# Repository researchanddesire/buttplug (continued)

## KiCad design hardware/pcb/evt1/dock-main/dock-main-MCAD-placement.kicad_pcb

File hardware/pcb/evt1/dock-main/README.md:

# Shared dock main PCB candidate

`dock-main.kicad_pcb` combines the 48 source-power, 44 controller and 58 safety electrical references on one four-layer, 1.00 mm board, with six mechanical holes. The original leaf circuits remain the schematic authority. The frozen routed board passes full native KiCad10.0.8 DRC with zero violations and zero unconnected items. Final source-bound checks and the saved-copper resistance report establish the digital candidate; this folder is not a fabrication release.

The fabrication quote candidate requests finished outer copper ≥35 µm, inner copper ≥30 µm, finished via bore ≥0.15 mm and via-wall plating ≥25 µm. Nominal “1 oz” labels do not establish these minima; supplier acceptance remains false. In1 is reserved for continuous ground; In2 contains separated power distribution and low-speed routes. F.Cu/B.Cu carry the remaining signals. Ordinary trace/clearance minima are 0.15/0.15 mm, with 0.50/0.20 mm through vias. The global hole clearance is 0.20 mm. `dock-main.kicad_dru` permits 0.15 mm only between J101-owned features to preserve the USB4105 manufacturer pattern, whose actual spacing is about 0.1751 mm; fabricator acceptance remains required.

The [bench quote packages](assembly-quote/README.md) bind the routed Main
to the matching 3.65 Ω UV boards and include bare-board and assembly options.

The source block's 192 copper objects are retained, along with all 207 main critical objects. Of 59 subsequently authored fanout objects, one graph-redundant one-layer via was retired; the remaining 58 retain their exact geometry and identities. `critical-routing.json` records the authored clock, local bypass, ADC and cut-switch power connections. The approved U615/H706 adjustment is bounded by `routing/u615-bounded-exception.json`. Short residual pad escapes and three ground stitches are recorded separately. `check_main.py` checks the saved native pad/net map, protected copper, screw-head clearances and complete native DRC without ignored checks or exclusions. It can explicitly refresh a regenerated schematic XML binding only after matching all 150 native references and every physical electrical pad.

The frozen `dock-main-MCAD-placement.kicad_pcb` is the StepUp input for parallel mechanical integration. It is a placement/model snapshot, not the final routed fabrication board. `mcad-placement-handoff.json`, `mcad-model-coverage.json` and `mcad-model-checks.json` bind its 138 physical package models and 12 copper-only positions. `check_mcad_geometry.py` compares the working board's outline, holes, component poses, pads, model transforms and actual model-file hashes against that snapshot.

The frame is `dockX = pcbX - 100`, `dockY = 200 - pcbY`, F.Cu toward dock +Z. Board bottom/top are Z5.4/6.4 mm. Bounds are X−48…48, Y−4…68 mm; the native bounding-box centre (100,168) maps to dock (0,32). The four original Ø2.3 mm holes remain at (−8,5.5), (8,5.5), (−8,23.5), (8,23.5); rear holes are (−44,64) and (44,55.7). Each retains an R3 surface copper/via hardware clearance. U615 is at (42,49.5); both selected horizontal GH header positions remain unchanged.

All package STEP files are local under `DockMain.3dshapes/`. They are attributed KiCad package-family models, four primary-dimensional TI package reconstructions and a selected USB4105 1.20 mm stake derivative. The custom parts have editable FreeCAD multi-body sources. They are not exact OEM CAD or received-part qualification. Sources, dimensions, omissions and licenses are recorded in `model-plan.json` and the model provenance files. The USB face remains at X0/Y−5 with its seating plane at Z6.4. Selected nominal stakes reach Z5.2; the manufacturer's ±0.15 mm stake tolerance still needs physical clearance qualification. The old Z5.1 datum is the enclosure window bottom.

The adopted power candidate uses a 4.10 V minimum driver input and a 50 mΩ hot/aged common PCB supply-plus-return allowance. `power-study/` contains native filled-copper masks, actual neck/via calculations and the independent DC tradeoff. `MFG-SPEC.md` and `build-constraints.json` state the requested finished minima and explicit supplier review of the native 0.10 mm J101 annular feature / bounded 0.15 mm hole-clearance pattern. The fabricator must confirm the dielectric build and process limits. The inner layers must not silently use 0.5 oz copper. Shared copper is charged at full source current, including device/UI/contact loops. The 70% efficiency assumption, current limits, startup/inrush, USB suspend/source changes and all hot/aged path limits require hardware measurements. Optical leakage, temperature, material aging and cleaning efficacy remain separate validation gates; no sterilization or powered result is claimed.

`build_main.py` is a guarded placement builder and refuses to overwrite routed work. Do not restart placement to refresh a report. `route_main.py` exchanges only supported wire/via records; its residual mode retains all completed native nets and every protected item. `fill_main.py` clears stale fill caches before rebuilding connectivity and asserts that refill preserves every authored copper net. The generic automatic stub-cleanup loop was stopped by approval review. The final single-segment removal used independent owner/root/peer terminal-path evidence, a fixed input SHA/UUID, and assertions that every other copper signature and zone identity remained intact. Future stub mutations require exact reviewed UUIDs and input SHA. Historical router checkpoints and preflight reports are development evidence, not acceptance reports. Only a current, source-bound final `native-checks.json` can establish complete digital routing checks.

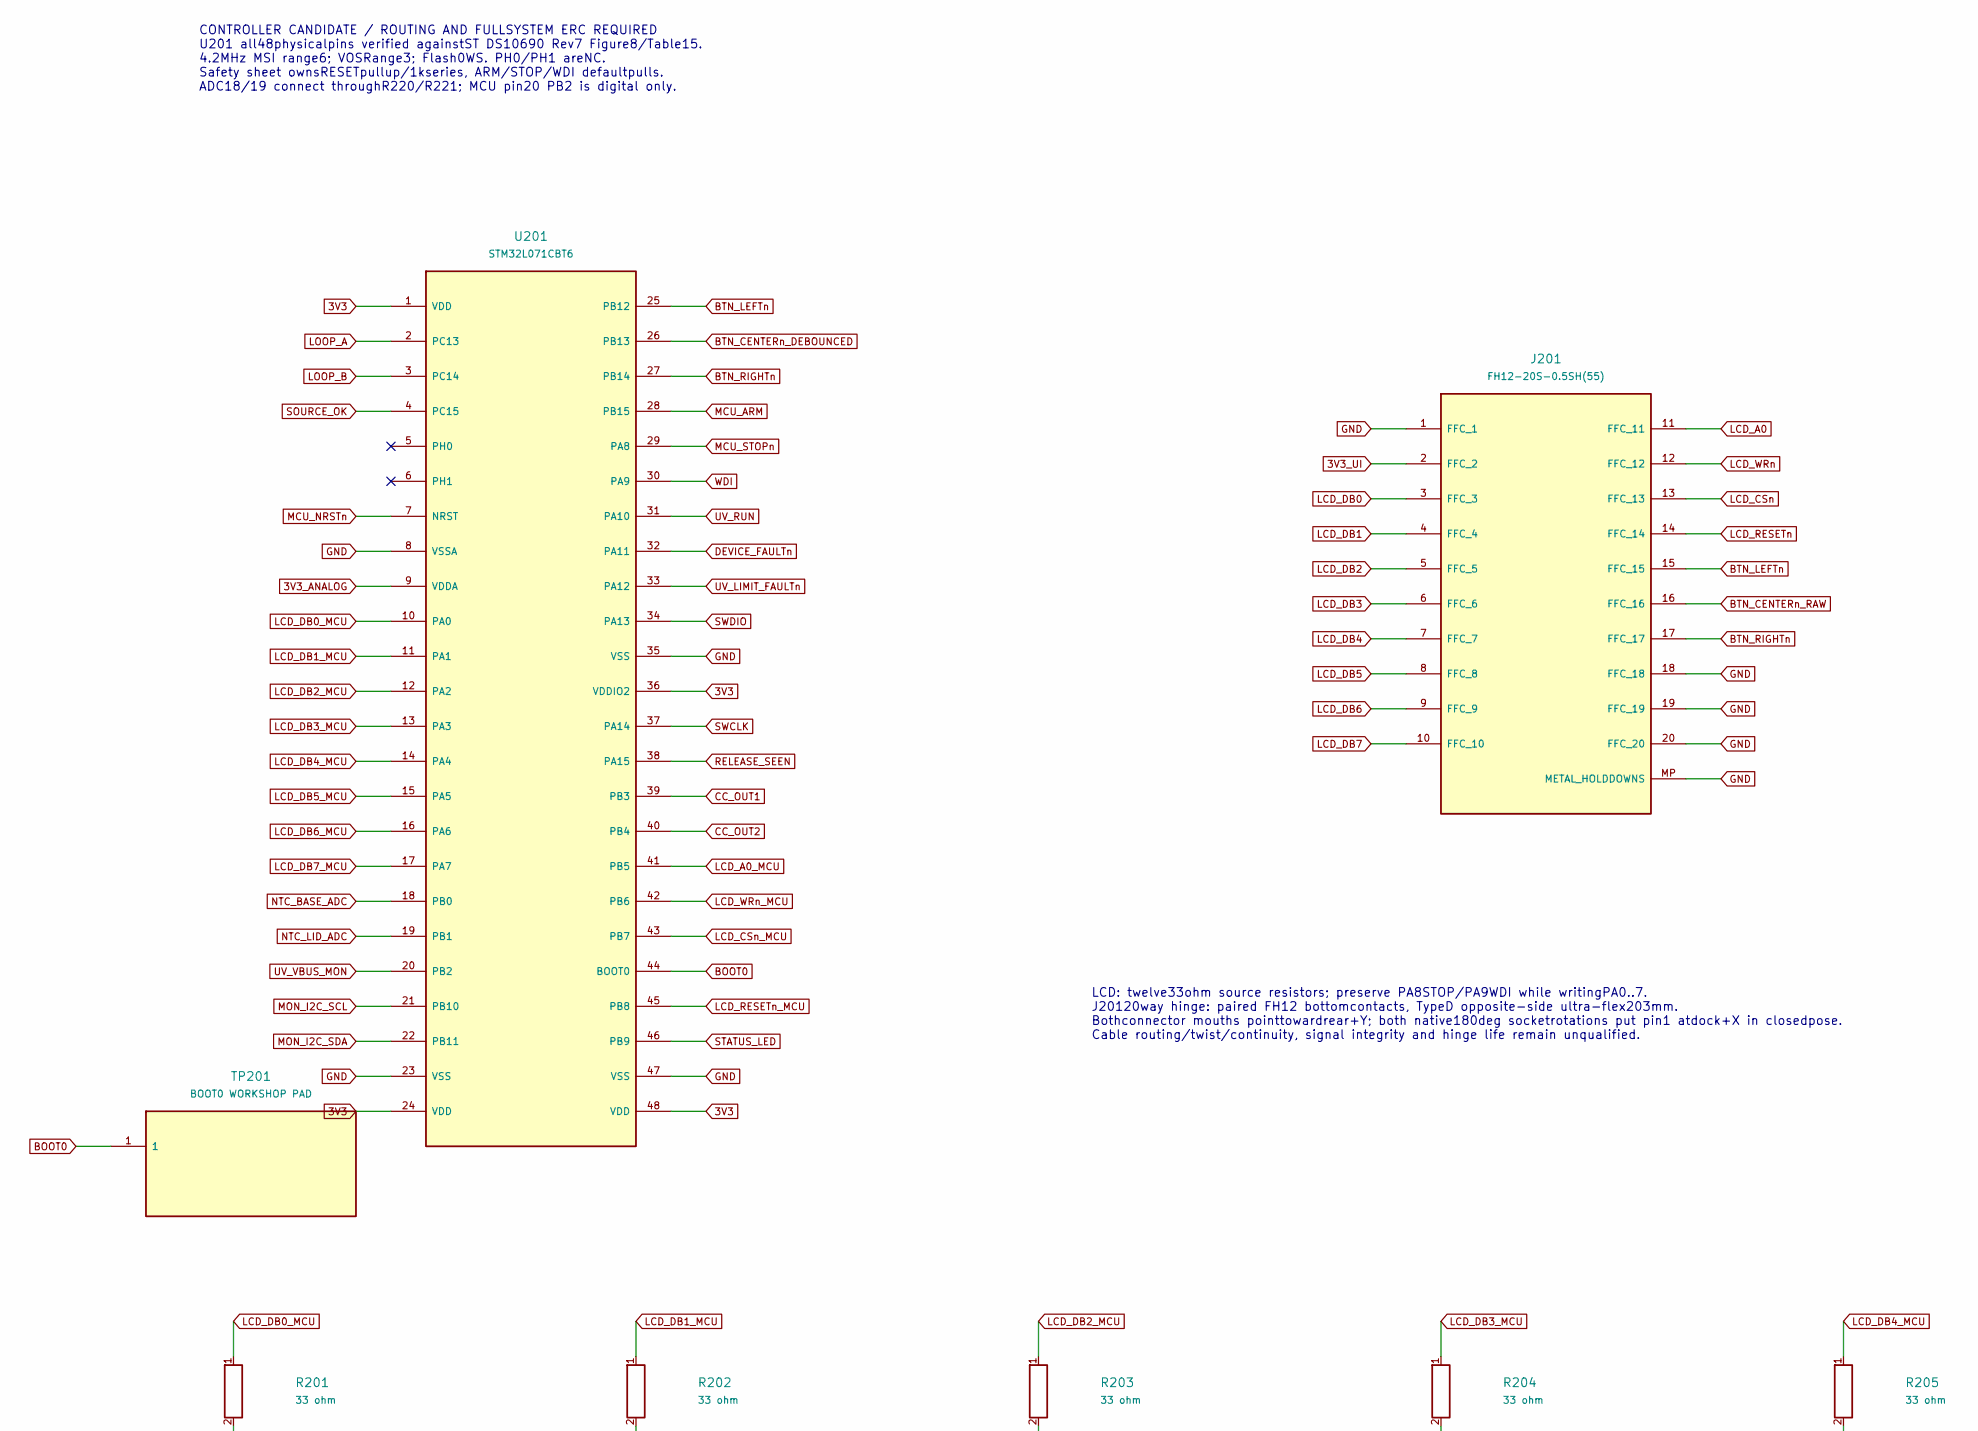
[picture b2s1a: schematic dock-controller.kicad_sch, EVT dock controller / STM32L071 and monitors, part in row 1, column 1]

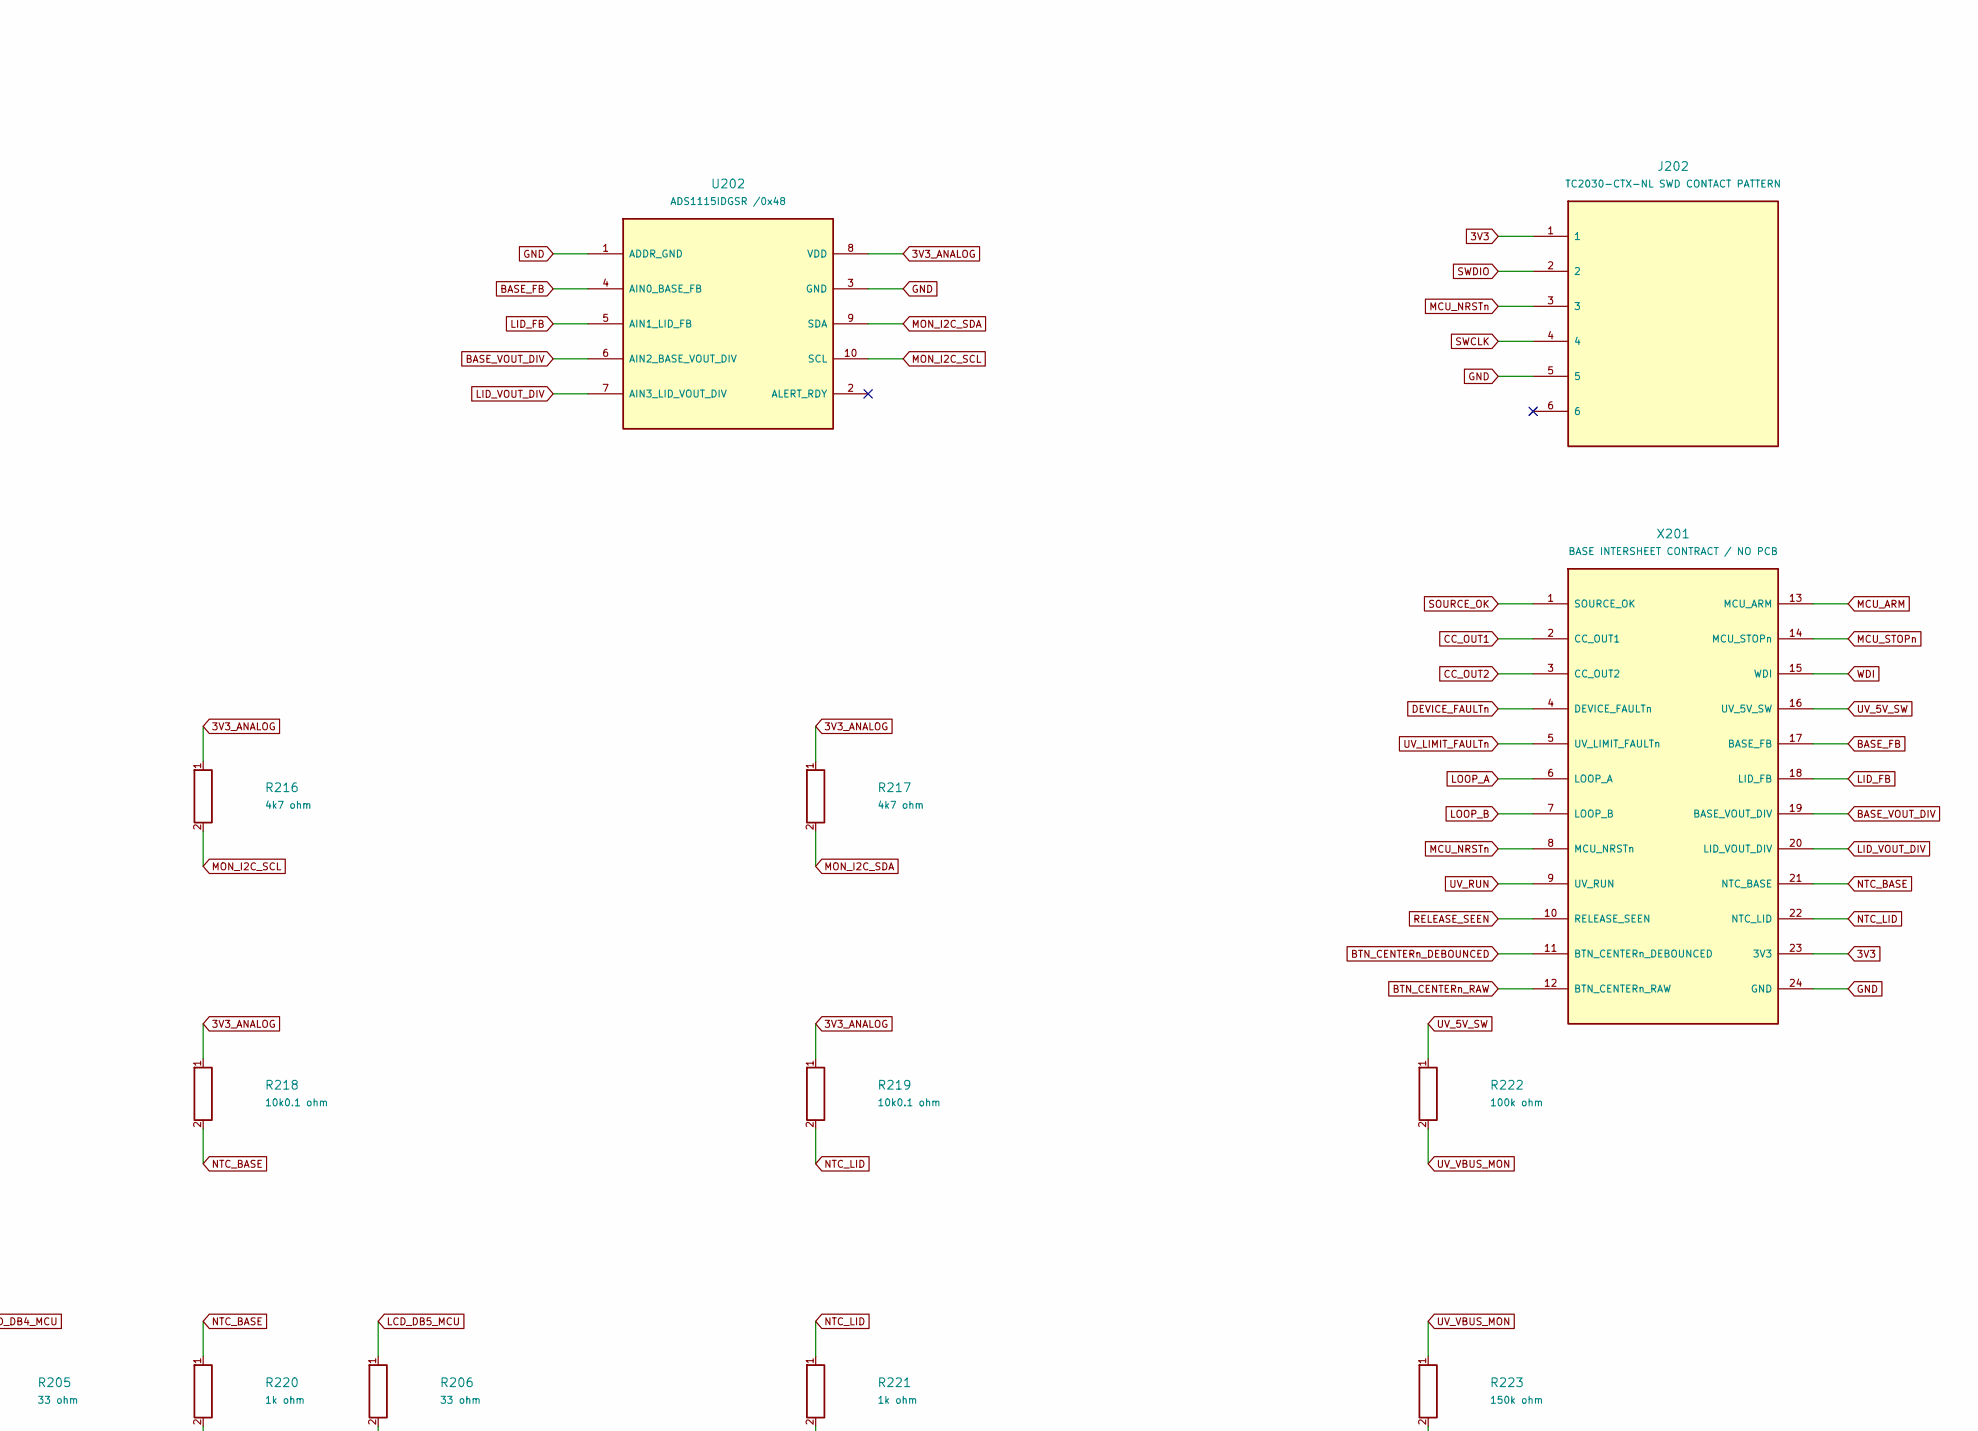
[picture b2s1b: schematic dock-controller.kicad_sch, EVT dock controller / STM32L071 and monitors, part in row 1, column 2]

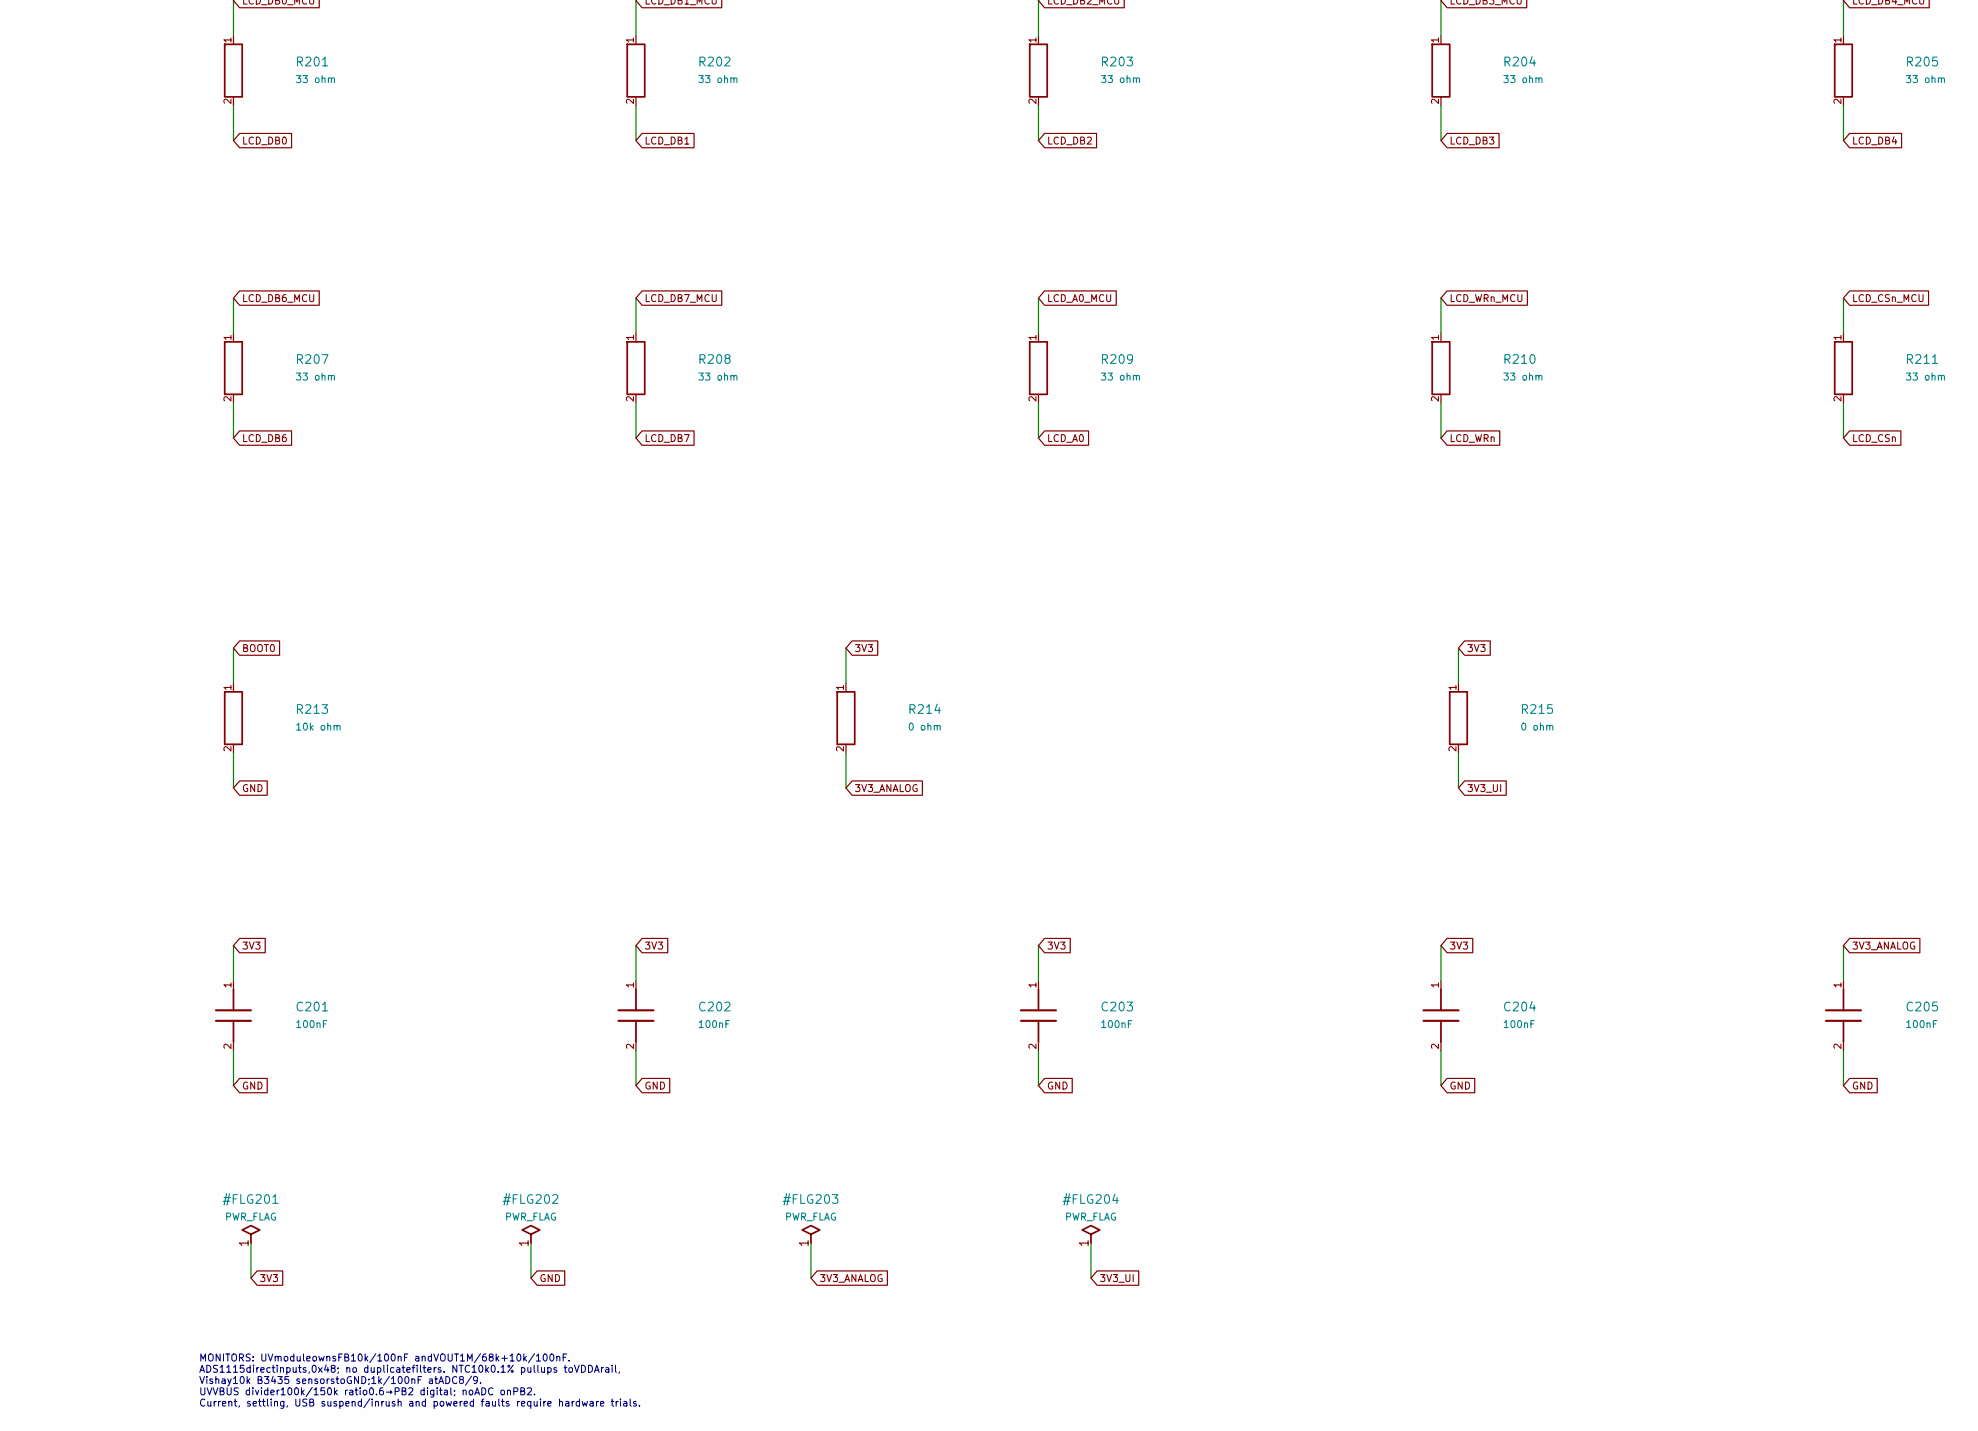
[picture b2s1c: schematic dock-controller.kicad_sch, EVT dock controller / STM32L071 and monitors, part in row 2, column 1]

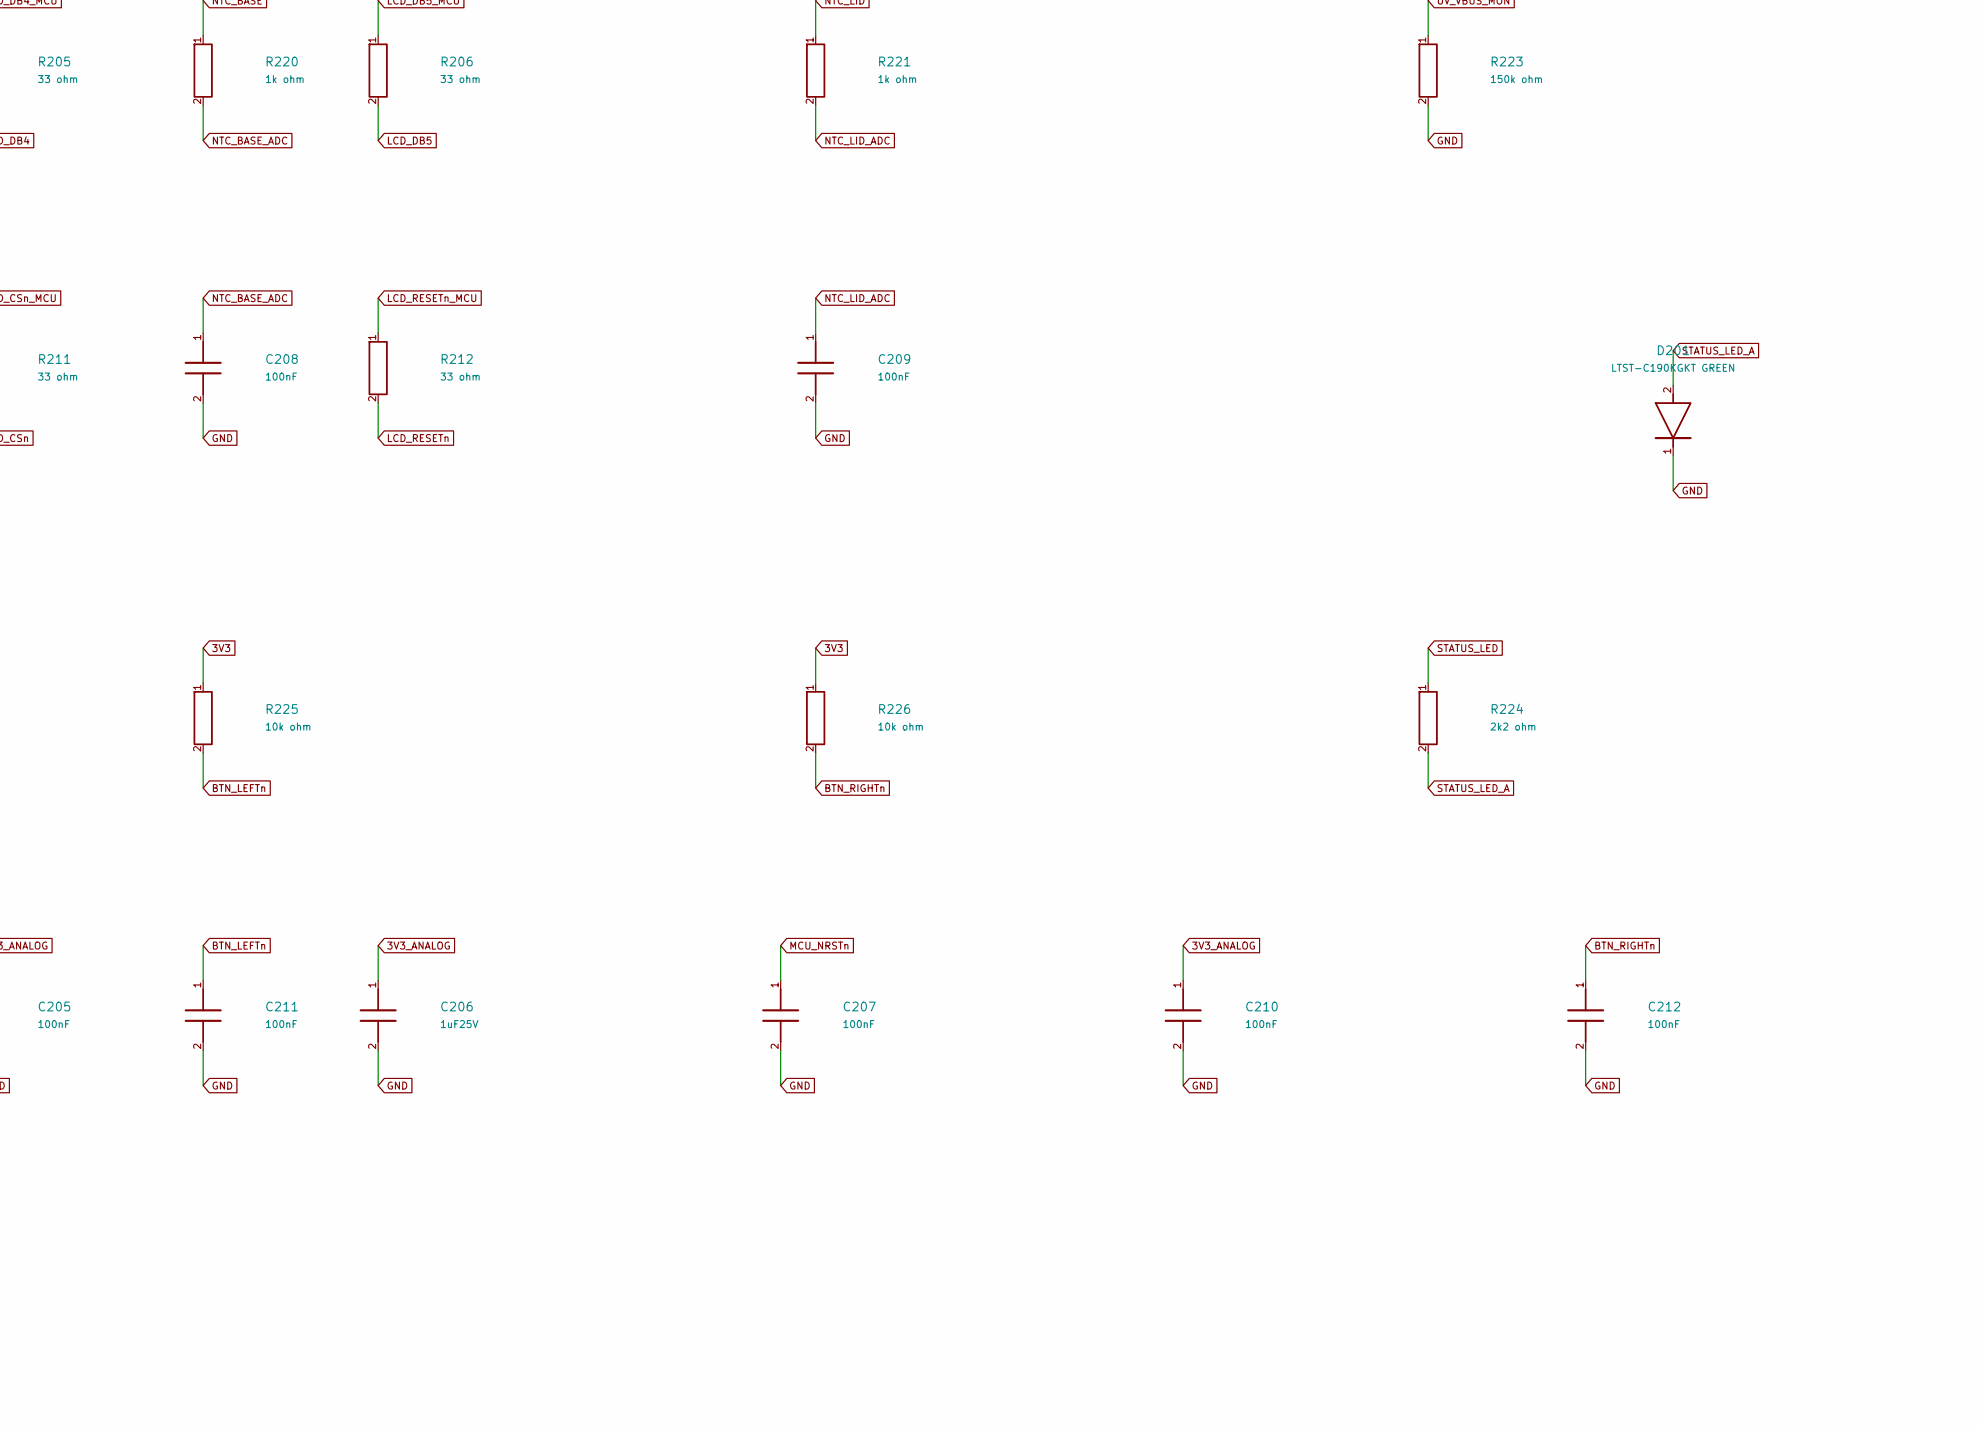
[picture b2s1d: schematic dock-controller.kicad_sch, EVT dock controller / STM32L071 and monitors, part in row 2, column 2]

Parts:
C201, C202, C203, C204, C205, C207, C208, C209, C210, C211, C212: 100nF; C_0402_1005Metric; MPN GRM155R71C104KA88D
C206: 1uF25V; C_0603_1608Metric; MPN C1608X7R1E105K080AB
D201: LTST-C190KGKT GREEN; LED_0603_1608Metric; MPN LTST-C190KGKT
J201: FH12-20S-0.5SH(55); Hirose_FH12-20S-0.5SH_1x20-1MP_P0.50mm_Horizontal; MPN FH12-20S-0.5SH(55)
J202: TC2030-CTX-NL SWD CONTACT PATTERN; Tag-Connect_TC2030-IDC-NL_2x03_P1.27mm_Vertical; MPN –
R201, R202, R203, R204, R205, R206, R207, R208, R209, R210, R211, R212: 33 ohm; R_0603_1608Metric; MPN RC0603FR-0733RL
R213, R225, R226: 10k ohm; R_0603_1608Metric; MPN RC0603FR-0710KL
R214, R215: 0 ohm; R_0603_1608Metric; MPN RC0603JR-070RL
R216, R217: 4k7 ohm; R_0603_1608Metric; MPN RC0603FR-074K7L
R218, R219: 10k0.1 ohm; R_0603_1608Metric; MPN RT0603BRD0710KL
R220, R221: 1k ohm; R_0603_1608Metric; MPN RC0603FR-071KL
R222: 100k ohm; R_0603_1608Metric; MPN RC0603FR-07100KL
R223: 150k ohm; R_0603_1608Metric; MPN RC0603FR-07150KL
R224: 2k2 ohm; R_0603_1608Metric; MPN RC0603FR-072K2L
TP201: BOOT0 WORKSHOP PAD; TestPoint_Pad_D1.0mm; MPN –
U201: STM32L071CBT6; LQFP-48_7x7mm_P0.5mm; MPN STM32L071CBT6
U202: ADS1115IDGSR /0x48; VSSOP-10_3x3mm_P0.5mm; MPN ADS1115IDGSR
X201: BASE INTERSHEET CONTRACT / NO PCB; MPN –

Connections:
3V3: C201.1, C202.1, C203.1, C204.1, J202.1, R214.1, R215.1, R225.1, R226.1, U201.1 (VDD), U201.24 (VDD), U201.36 (VDDIO2), U201.48 (VDD), X201.23 (3V3); also elsewhere on the board
3V3_ANALOG: C205.1, C206.1, C210.1, R214.2, R216.1, R217.1, R218.1, R219.1, U201.9 (VDDA), U202.8 (VDD)
3V3_UI: J201.2 (FFC_2), R215.2
BASE_FB: U202.4 (AIN0_BASE_FB), X201.17 (BASE_FB); also elsewhere on the board
BASE_VOUT_DIV: U202.6 (AIN2_BASE_VOUT_DIV), X201.19 (BASE_VOUT_DIV); also elsewhere on the board
BOOT0: R213.1, TP201.1, U201.44 (BOOT0)
BTN_CENTERn_DEBOUNCED: U201.26 (PB13), X201.11 (BTN_CENTERn_DEBOUNCED); also elsewhere on the board
BTN_CENTERn_RAW: J201.16 (FFC_16), X201.12 (BTN_CENTERn_RAW); also elsewhere on the board
BTN_LEFTn: C211.1, J201.15 (FFC_15), R225.2, U201.25 (PB12)
BTN_RIGHTn: C212.1, J201.17 (FFC_17), R226.2, U201.27 (PB14)
CC_OUT1: U201.39 (PB3), X201.2 (CC_OUT1); also elsewhere on the board
CC_OUT2: U201.40 (PB4), X201.3 (CC_OUT2); also elsewhere on the board
DEVICE_FAULTn: U201.32 (PA11), X201.4 (DEVICE_FAULTn); also elsewhere on the board
GND: C201.2, C202.2, C203.2, C204.2, C205.2, C206.2, C207.2, C208.2, C209.2, C210.2, C211.2, C212.2, D201.1 (2), J201.1 (FFC_1), J201.18 (FFC_18), J201.19 (FFC_19), J201.20 (FFC_20), J201.MP (METAL_HOLDDOWNS), J202.5, R213.2, R223.2, U201.8 (VSSA), U201.23 (VSS), U201.35 (VSS), U201.47 (VSS), U202.1 (ADDR_GND), U202.3 (GND), X201.24 (GND); also elsewhere on the board
LCD_A0: J201.11 (FFC_11), R209.2
LCD_A0_MCU: R209.1, U201.41 (PB5)
LCD_CSn: J201.13 (FFC_13), R211.2
LCD_CSn_MCU: R211.1, U201.43 (PB7)
LCD_DB0: J201.3 (FFC_3), R201.2
LCD_DB0_MCU: R201.1, U201.10 (PA0)
LCD_DB1: J201.4 (FFC_4), R202.2
LCD_DB1_MCU: R202.1, U201.11 (PA1)
LCD_DB2: J201.5 (FFC_5), R203.2
LCD_DB2_MCU: R203.1, U201.12 (PA2)
LCD_DB3: J201.6 (FFC_6), R204.2
LCD_DB3_MCU: R204.1, U201.13 (PA3)
LCD_DB4: J201.7 (FFC_7), R205.2
LCD_DB4_MCU: R205.1, U201.14 (PA4)
LCD_DB5: J201.8 (FFC_8), R206.2
LCD_DB5_MCU: R206.1, U201.15 (PA5)
LCD_DB6: J201.9 (FFC_9), R207.2
LCD_DB6_MCU: R207.1, U201.16 (PA6)
LCD_DB7: J201.10 (FFC_10), R208.2
LCD_DB7_MCU: R208.1, U201.17 (PA7)
LCD_RESETn: J201.14 (FFC_14), R212.2
LCD_RESETn_MCU: R212.1, U201.45 (PB8)
LCD_WRn: J201.12 (FFC_12), R210.2
LCD_WRn_MCU: R210.1, U201.42 (PB6)
LID_FB: U202.5 (AIN1_LID_FB), X201.18 (LID_FB); also elsewhere on the board
LID_VOUT_DIV: U202.7 (AIN3_LID_VOUT_DIV), X201.20 (LID_VOUT_DIV); also elsewhere on the board
LOOP_A: U201.2 (PC13), X201.6 (LOOP_A); also elsewhere on the board
LOOP_B: U201.3 (PC14), X201.7 (LOOP_B); also elsewhere on the board
MCU_ARM: U201.28 (PB15), X201.13 (MCU_ARM); also elsewhere on the board
MCU_NRSTn: C207.1, J202.3, U201.7 (NRST), X201.8 (MCU_NRSTn); also elsewhere on the board
MCU_STOPn: U201.29 (PA8), X201.14 (MCU_STOPn); also elsewhere on the board
MON_I2C_SCL: R216.2, U201.21 (PB10), U202.10 (SCL)
MON_I2C_SDA: R217.2, U201.22 (PB11), U202.9 (SDA)
NTC_BASE: R218.2, R220.1, X201.21 (NTC_BASE); also elsewhere on the board
NTC_BASE_ADC: C208.1, R220.2, U201.18 (PB0)
NTC_LID: R219.2, R221.1, X201.22 (NTC_LID); also elsewhere on the board
NTC_LID_ADC: C209.1, R221.2, U201.19 (PB1)
RELEASE_SEEN: U201.38 (PA15), X201.10 (RELEASE_SEEN); also elsewhere on the board
SOURCE_OK: U201.4 (PC15), X201.1 (SOURCE_OK); also elsewhere on the board
STATUS_LED: R224.1, U201.46 (PB9)
STATUS_LED_A: D201.2 (1), R224.2
SWCLK: J202.4, U201.37 (PA14)
SWDIO: J202.2, U201.34 (PA13)
UV_5V_SW: R222.1, X201.16 (UV_5V_SW); also elsewhere on the board
UV_LIMIT_FAULTn: U201.33 (PA12), X201.5 (UV_LIMIT_FAULTn); also elsewhere on the board
UV_RUN: U201.31 (PA10), X201.9 (UV_RUN); also elsewhere on the board
UV_VBUS_MON: R222.2, R223.1, U201.20 (PB2)
WDI: U201.30 (PA9), X201.15 (WDI); also elsewhere on the board

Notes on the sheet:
CONTROLLER CANDIDATE / ROUTING AND FULLSYSTEM ERC REQUIRED U201 all48physicalpins verified againstST DS10690 Rev7 Figure8/Table15. 4.2MHz MSI range6; VOSRange3; Flash0WS. PH0/PH1 areNC. Safety sheet ownsRESETpullup/1kseries, ARM/STOP/WDI defaultpulls. ADC18/19 connect throughR220/R221; MCU pin20 PB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
LCD: twelve33ohm source resistors; preserve PA8STOP/PA9WDI while writingPA0..7. J20120way hinge: paired FH12 bottomcontacts, TypeD opposite-side ultra-flex203mm. Bothconnector mouths pointtowardrear+Y; both native180deg socketrotations put pin1 atdock+X in closedpose. Cable routing/twist/continuity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
MONITORS: UVmoduleownsFB10k/100nF andVOUT1M/68k+10k/100nF. ADS1115directinputs,0x48; no duplicatefilters. NTC10k0.1% pullups toVDDArail, Vishay10k B3435 sensorstoGND;1k/100nF atADC8/9. UVVBUS divider100k/150k ratio0.6→PB2 digital; noADC onPB2. Current, settling, USB suspend/inrush and powered fault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

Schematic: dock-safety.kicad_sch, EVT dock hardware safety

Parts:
C602, C606, C607, C608, C609, C610, C611, C612, C613, C614, C615, C616: 100nF16V; C_0402_1005Metric; MPN GRM155R71C104KA88D
C620, C621, C622: 1uF25V; C_0603_1608Metric; MPN C1608X7R1E105K080AB
C623, C624: 1nF50V C0G; C_0603_1608Metric; MPN C1608C0G1H102J080AA
J601, J602: SM02B-GHS-TB; JST_GH_SM02B-GHS-TB_1x02-1MP_P1.25mm_Horizontal; MPN SM02B-GHS-TB(LF)(SN)
J621, J622: SM08B-GHS-TB; JST_GH_SM08B-GHS-TB_1x08-1MP_P1.25mm_Horizontal; MPN SM08B-GHS-TB(LF)(SN)
R601, R603, R607, R616: 10k 1%; R_0603_1608Metric; MPN RC0603FR-0710KL
R602, R604, R605, R608, R612, R613, R617: 100k 1%; R_0603_1608Metric; MPN RC0603FR-07100KL
R606: 1k 1%; R_0603_1608Metric; MPN RC0603FR-071KL
R610, R611: 330R 1%; R_0805_2012Metric; MPN CRCW0805330RFKEA
R614, R615: 430R 1%; R_0805_2012Metric; MPN CRCW0805430RFKEA
R618: 1M 1%; R_0603_1608Metric; MPN RC0603FR-071ML
R619: 47k 1%; R_0603_1608Metric; MPN RC0603FR-0747KL
S601, S602: D2F-01L remote; MPN D2F-01L
TP601: MCU_NRSTn; TestPoint_Pad_D1.0mm; MPN Cu_D1.0mm_test_land
TP602: BASE_FB; TestPoint_Pad_D1.0mm; MPN Cu_D1.0mm_test_land
TP603: LID_FB; TestPoint_Pad_D1.0mm; MPN Cu_D1.0mm_test_land
TP604: BASE_VOUT_DIV; TestPoint_Pad_D1.0mm; MPN Cu_D1.0mm_test_land
TP605: LID_VOUT_DIV; TestPoint_Pad_D1.0mm; MPN Cu_D1.0mm_test_land
TP606: NTC_BASE; TestPoint_Pad_D1.0mm; MPN Cu_D1.0mm_test_land
TP607: NTC_LID; TestPoint_Pad_D1.0mm; MPN Cu_D1.0mm_test_land
U602: TPS22919DCKR; SOT-363_SC-70-6; MPN TPS22919DCKR
U606: TPS3431SDRBR; Texas_DRB0008A_3x3mm_P0.65_EP_Fingers; MPN TPS3431SDRBR
U607, U616: TPS3808G33DBVR; SOT-23-6; MPN TPS3808G33DBVR
U608: MAX6816EUS+T; SOT-143; MPN MAX6816EUS+T
U609: SN74LVC74APWR; TSSOP-14_4.4x5mm_P0.65mm; MPN SN74LVC74APWR
U610, U611: TPS22992RXPR; Texas_RXP0008A_1.25x1.5mm_Asymmetric; MPN TPS22992RXPR
U612: SN74HCS21PWR; TSSOP-14_4.4x5mm_P0.65mm; MPN SN74HCS21PWR
U613, U614: SN74LVC2G17DCKR; SOT-363_SC-70-6; MPN SN74LVC2G17DCKR
U615: SN74HCS08PWR; TSSOP-14_4.4x5mm_P0.65mm; MPN SN74HCS08PWR

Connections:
3V3: C606.1, C607.1, C608.1, C609.1, C612.1, C613.1, C614.1, C615.1, C616.1, R601.1, R603.1, R607.1, R608.1, R616.1, R617.1, U606.1 (VDD), U606.3 (EN_HARD_HIGH), U606.5 (SET1_HIGH), U607.3 (MR_N), U607.5 (SENSE), U607.6 (VDD), U608.4 (VCC), U609.2 (1D), U609.4 (1PRE_N), U609.10 (2PRE_N), U609.14 (VCC), U612.13 (2D), U612.14 (VCC), U613.5 (VCC), U614.5 (VCC), U615.14 (VCC), U616.5 (SENSE), U616.6 (VDD); also elsewhere on the board
ARM_D: U609.12 (2D_ARM), U615.3 (1Y_ARM_D)
BASE_FB: J621.4, TP602.1; also elsewhere on the board
BASE_THERM_SEND: J601.2, J621.7, S601.NO (NO_LID_CLOSED)
BASE_VOUT_DIV: J621.5, TP604.1; also elsewhere on the board
BTN_CENTER_PRESSED: R619.1, U614.3 (2A_LOOP_B); also elsewhere on the board
BTN_CENTERn_DEBOUNCED: U608.3 (OUT_DEBOUNCED), U614.1 (1A_LOOP_A); also elsewhere on the board
BTN_CENTERn_RAW: R617.2, U608.2 (IN_RAW); also elsewhere on the board
CLEARn: U609.1 (1CLR_N), U609.13 (2CLR_N), U612.8 (2Y_CLEAR_N)
CLOCK_PRESS: U609.11 (2CLK_PRESS), U614.4 (2Y_LOOP_B)
CLOCK_RELEASE: U609.3 (1CLK_RELEASE), U614.6 (1Y_LOOP_A)
CUT_A_CT: C623.1, U610.7 (CT)
CUT_A_QOD: R610.2, U610.5 (QOD)
CUT_B_CT: C624.1, U611.7 (CT)
CUT_B_QOD: R611.2, U611.5 (QOD)
GND: C602.2, C606.2, C607.2, C608.2, C609.2, C610.2, C611.2, C612.2, C613.2, C614.2, C615.2, C616.2, C620.2, C621.2, C622.2, C623.2, C624.2, J601.MP (MOUNT_GND), J602.MP (MOUNT_GND), J621.2, J621.MP (MOUNT_GND), J622.2, J622.MP (MOUNT_GND), R602.2, R604.2, R605.2, R612.2, R613.2, R614.2, R615.2, R618.2, R619.2, U602.2 (GND), U606.4 (GND), U606.9 (EP_GND), U607.2 (GND), U608.1 (GND), U609.7 (GND), U610.4 (GND), U611.4 (GND), U612.7 (GND), U613.2 (GND), U614.2 (GND), U615.7 (GND), U616.2 (GND); also elsewhere on the board
HOST_5V: C602.1, C610.1, C611.1, U602.1 (VIN), U610.1 (VBIAS), U611.1 (VBIAS); also elsewhere on the board
LID_FB: J622.4, TP603.1; also elsewhere on the board
LID_THERM_SEND: J602.2, J622.7, S602.NO (NO_LID_CLOSED)
LID_VOUT_DIV: J622.5, TP605.1; also elsewhere on the board
LOOP_5V: J601.1, J602.1, S601.C (COM), S602.C (COM), U602.5 (QOD), U602.6 (VOUT)
LOOP_A: U612.1 (1A), U613.6 (1Y_LOOP_A), U615.4 (2A); also elsewhere on the board
LOOP_A_RAW: J621.8, R614.1, U613.1 (1A_LOOP_A)
LOOP_B: U612.2 (1B), U613.4 (2Y_LOOP_B), U615.10 (3B); also elsewhere on the board
LOOP_B_RAW: J622.8, R615.1, U613.3 (2A_LOOP_B)
MCU_ARM: R604.1, U615.2 (1B); also elsewhere on the board
MCU_NRSTn: R606.2, TP601.1; also elsewhere on the board
MCU_STOPn: R605.1, U612.10 (2B); also elsewhere on the board
NTC_BASE: J621.6, TP606.1; also elsewhere on the board
NTC_LID: J622.6, TP607.1; also elsewhere on the board
RAW_SAFE: U612.6 (1Y_RAW_SAFE), U612.9 (2A), U616.3 (MR_N)
RELEASE_SEEN: U609.5 (1Q_RELEASE_SEEN), U615.1 (1A); also elsewhere on the board
SAFE_RESETn: R601.2, R606.1, U606.7 (WDO_N), U606.8 (ENOUT), U607.1 (RESET_N), U612.5 (1D)
SOURCE_OK: R618.1, U602.3 (ON), U612.4 (1C), U615.5 (2B); also elsewhere on the board
UV_5V_LIMITED: C620.1, U610.2 (VIN); also elsewhere on the board
UV_5V_MID: C621.1, R610.1, U610.6 (VOUT), U611.2 (VIN)
UV_5V_SW: C622.1, J621.1, J622.1, R611.1, U611.6 (VOUT); also elsewhere on the board
UV_CTRL: J621.3, J622.3, U615.11 (4Y_UV_CTRL)
UV_DELAY_CT: R608.2, U616.4 (CT)
UV_DELAYn: R607.2, U612.12 (2C), U616.1 (RESET_N)
UV_GATE_A: R612.1, U610.8 (ON), U615.6 (2Y_CUT_A)
UV_GATE_B: R613.1, U611.8 (ON), U615.8 (3Y_CUT_B)
UV_POWER_GOOD: R616.2, U611.3 (PG), U615.13 (4B)
UV_RUN: U609.9 (2Q_UV_RUN), U615.9 (3A), U615.12 (4A); also elsewhere on the board
WDI: R602.1, U606.6 (WDI); also elsewhere on the board
WDT_CWD: R603.2, U606.2 (CWD)

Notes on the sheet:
HARDWARE INTERFACES: inputs3V3/HOST5/UV5LIMITED/SOURCE_OK fromdocksource. MCUinputsARM,STOPn,WDI defaultLOW. CENTERdebouncedOUT goes tosourceU114pin3; sourceU114pin4returnsBTN_CENTER_PRESSED. MCU_NRSTn isseparatefromSAFE_RESETn byR6061k tolimit100nF localresetcapdischarge.
DUALPHYSICALLOOPS: qualifiedHOST5 -> D2F NO -> respectiveUVmodule67L045NC -> LOOP_RAW ->430RGND. Thermostatlowlevelreference10mA: eachloop10.35mAmin/12.34mAmax. U602turnsloopsoff onlegacyUSB. DisconnectedwirepreventsUV. Bothlatchesclear onfault/STOP; watchdogrecoverygetsUVdelay. Release,thenfreshpr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
UV powercutsuseTPS22992lowRON insteadTPS22919. QOD330R ispopulated. PGonlygatesboostCTRL, notUV_RUN. Fullsource/cablelossbudget, hardwaretiming/shutdown opticaltail andsinglefaulttests remainunqualified. PWR_FLAGs identifyexternalrails inthisstandalonecandidate; theyarenotboardcomponents. NO steril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
